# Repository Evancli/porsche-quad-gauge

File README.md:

# QUAD GAUGE FOR A PORSCHE 914
More info [here](https://evanli.com/quad-gauge-for-a-porsche-914/).

## Required Items
This gauge uses salvaged components from a Porsche 944 fuel gauge; the bezel, glass, and face plate. You can used the vintage gauges from the 944 or the corresponding gauges from your 914. It also required two new VDO gauges for voltage and oil pressure.

## Disassembly Tips
It's quite laborious to open these VDO gauges, even with the right tools. A prying spudger and flat implement are needed. Lots of care and attention to not mess up the sheet metal. Be very careful when you pry open the 944 fuel gauge. It's very easy damage the surface finish of the bezel. 

## Processes
The build uses 3D printed parts as well a laser cut and etched parts. 

## License
Shield: [![CC BY-SA 4.0][cc-by-sa-shield]][cc-by-sa]

This work is licensed under a
[Creative Commons Attribution-ShareAlike 4.0 International License][cc-by-sa].

[![CC BY-SA 4.0][cc-by-sa-image]][cc-by-sa]

[cc-by-sa]: http://creativecommons.org/licenses/by-sa/4.0/
[cc-by-sa-image]: https://licensebuttons.net/l/by-sa/4.0/88x31.png
[cc-by-sa-shield]: https://img.shields.io/badge/License-CC%20BY--SA%204.0-lightgrey.svg

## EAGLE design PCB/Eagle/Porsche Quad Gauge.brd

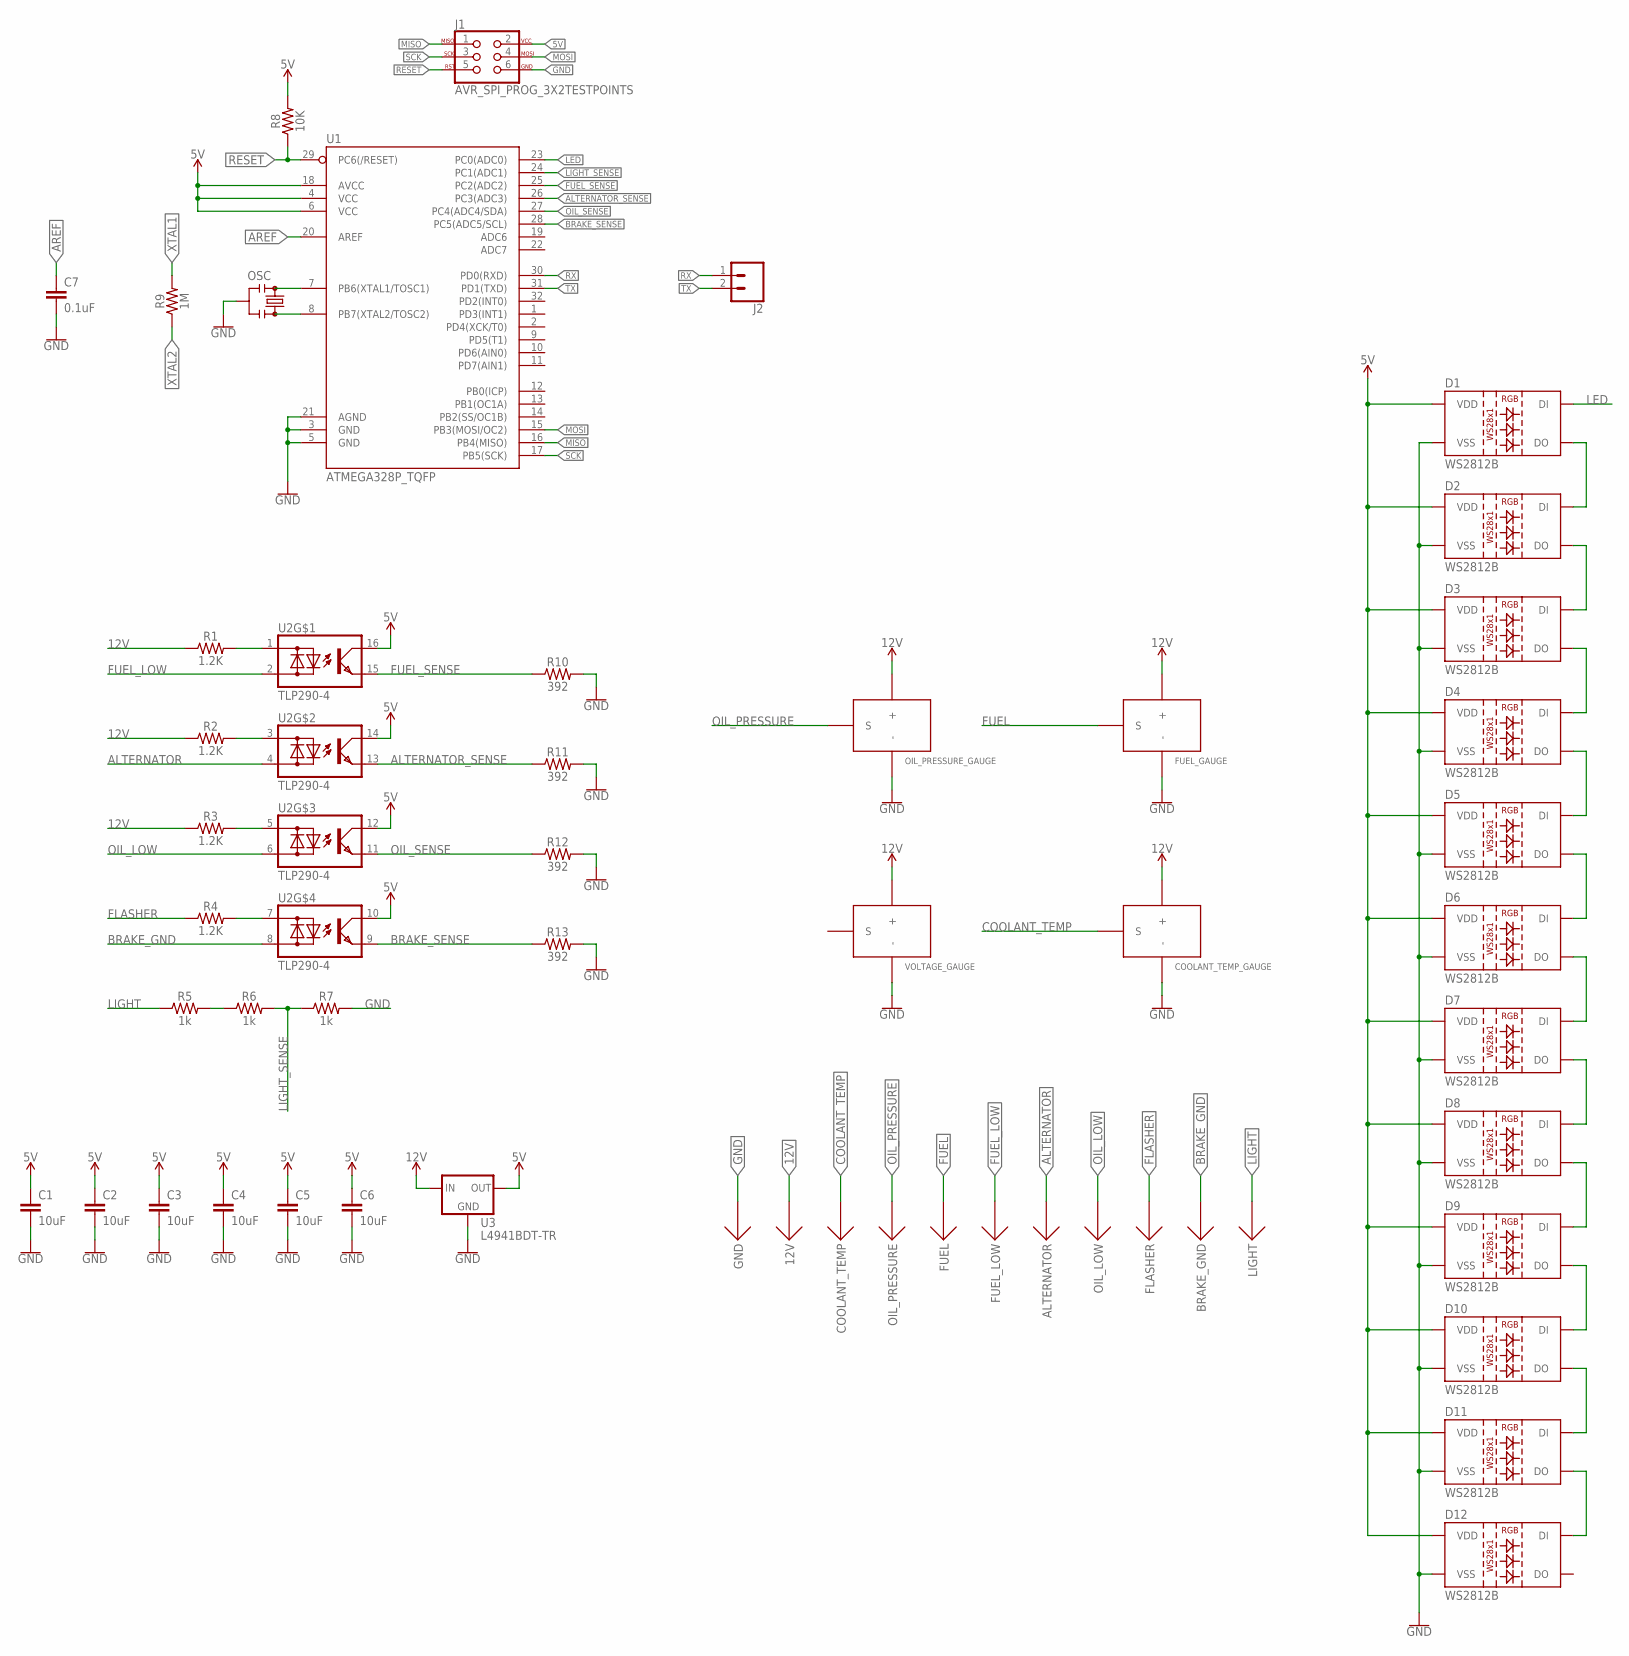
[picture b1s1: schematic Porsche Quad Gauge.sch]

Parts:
12V: CONNECTOR_QC_TAB_0.25; CONNECTOR_QC_TAB-0.25
ALTERNATOR: CONNECTOR_QC_TAB_0.25; CONNECTOR_QC_TAB-0.25
BRAKE_GND: CONNECTOR_QC_TAB_0.25; CONNECTOR_QC_TAB-0.25
C1, C2, C3, C4, C5, C6: 10uF; 0805
C7: 0.1uF; 0805
COOLANT_TEMP: CONNECTOR_QC_TAB_0.25; CONNECTOR_QC_TAB-0.25
COOLANT_TEMP_GAUGE: VDO_OLD; VDO_GAUGE_SOCKET
D1, D2, D3, D4, D5, D6, D7, D8, D9, D10, D11, D12: WS2812B
FLASHER: CONNECTOR_QC_TAB_0.25; CONNECTOR_QC_TAB-0.25
FUEL: CONNECTOR_QC_TAB_0.25; CONNECTOR_QC_TAB-0.25
FUEL_GAUGE: VDO_OLD; VDO_GAUGE_SOCKET
FUEL_LOW: CONNECTOR_QC_TAB_0.25; CONNECTOR_QC_TAB-0.25
GND: CONNECTOR_QC_TAB_0.25; CONNECTOR_QC_TAB-0.25
J1: AVR_SPI_PROG_3X2TESTPOINTS; 2X3_TEST_POINTS
J2: CONN_02; 1X02
LIGHT: CONNECTOR_QC_TAB_0.25; CONNECTOR_QC_TAB-0.25
OIL_LOW: CONNECTOR_QC_TAB_0.25; CONNECTOR_QC_TAB-0.25
OIL_PRESSURE: CONNECTOR_QC_TAB_0.25; CONNECTOR_QC_TAB-0.25
OIL_PRESSURE_GAUGE: VDO_NEW; VDO_NEW_GAUGE_SOCKET
OSC: PRQC16.00SR1010V00L; 3-SMD
R1, R2, R3, R4: 1.2K; 0805
R5, R6, R7: 1k; 0805
R8: 10K; 0805
R9: 1M; 0805
R10, R11, R12, R13: 392; 0805
U1: ATMEGA328P_TQFP; TQFP32-08
U2: TLP290-4; SO16
U3: L4941BDT-TR; D-PAK_TO252AA
VOLTAGE_GAUGE: VDO_NEW; VDO_NEW_GAUGE_SOCKET

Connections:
5V: C1.1, C2.1, C3.1, C4.1, C5.1, C6.1, D1.1 (VDD), D2.1 (VDD), D3.1 (VDD), D4.1 (VDD), D5.1 (VDD), D6.1 (VDD), D7.1 (VDD), D8.1 (VDD), D9.1 (VDD), D10.1 (VDD), D11.1 (VDD), D12.1 (VDD), J1.2, R8.2, U1.4 (VCC), U1.6 (VCC), U1.18 (AVCC), U2.10 (C), U2.12 (C), U2.14 (C), U2.16 (C), U3.3 (OUT)
12V: 12V.S1, 12V.S2, COOLANT_TEMP_GAUGE.12V (+), FUEL_GAUGE.12V (+), OIL_PRESSURE_GAUGE.12V (+), R1.1, R2.1, R3.1, U3.1 (IN), VOLTAGE_GAUGE.12V (+)
ALTERNATOR: ALTERNATOR.S1, ALTERNATOR.S2, U2.4 (AC2)
ALTERNATOR_SENSE: R11.1, U1.26 (PC3(ADC3)), U2.13 (E)
AREF: C7.1, U1.20 (AREF)
BRAKE_GND: BRAKE_GND.S1, BRAKE_GND.S2, U2.8 (AC2)
BRAKE_SENSE: R13.1, U1.28 (PC5(ADC5/SCL)), U2.9 (E)
COOLANT_TEMP: COOLANT_TEMP.S1, COOLANT_TEMP.S2, COOLANT_TEMP_GAUGE.SIGNAL (S)
FLASHER: FLASHER.S1, FLASHER.S2, R4.1
FUEL: FUEL.S1, FUEL.S2, FUEL_GAUGE.SIGNAL (S)
FUEL_LOW: FUEL_LOW.S1, FUEL_LOW.S2, U2.2 (AC2)
FUEL_SENSE: R10.1, U1.25 (PC2(ADC2)), U2.15 (E)
GND: C1.2, C2.2, C3.2, C4.2, C5.2, C6.2, C7.2, COOLANT_TEMP_GAUGE.GND (-), D1.3 (VSS), D2.3 (VSS), D3.3 (VSS), D4.3 (VSS), D5.3 (VSS), D6.3 (VSS), D7.3 (VSS), D8.3 (VSS), D9.3 (VSS), D10.3 (VSS), D11.3 (VSS), D12.3 (VSS), FUEL_GAUGE.GND (-), GND.S1, GND.S2, J1.6, OIL_PRESSURE_GAUGE.GND (-), OSC.GND (2), R7.2, R10.2, R11.2, R12.2, R13.2, U1.3 (GND), U1.5 (GND), U1.21 (AGND), U3.2 (GND), VOLTAGE_GAUGE.GND (-)
LED: D1.4 (DI), U1.23 (PC0(ADC0))
LIGHT: LIGHT.S1, LIGHT.S2, R5.1
LIGHT_SENSE: R6.2, R7.1, U1.24 (PC1(ADC1))
MISO: J1.1, U1.16 (PB4(MISO))
MOSI: J1.4, U1.15 (PB3(MOSI/OC2))
unnamed: R1.2, U2.1 (AC1)
unnamed: R5.2, R6.1
unnamed: R2.2, U2.3 (AC1)
unnamed: D1.2 (DO), D2.4 (DI)
unnamed: D2.2 (DO), D3.4 (DI)
unnamed: D3.2 (DO), D4.4 (DI)
unnamed: D4.2 (DO), D5.4 (DI)
unnamed: D5.2 (DO), D6.4 (DI)
unnamed: D6.2 (DO), D7.4 (DI)
unnamed: D7.2 (DO), D8.4 (DI)
unnamed: D8.2 (DO), D9.4 (DI)
unnamed: D9.2 (DO), D10.4 (DI)
unnamed: D10.2 (DO), D11.4 (DI)
unnamed: D11.2 (DO), D12.4 (DI)
unnamed: R3.2, U2.5 (AC1)
unnamed: R4.2, U2.7 (AC1)
OIL_LOW: OIL_LOW.S1, OIL_LOW.S2, U2.6 (AC2)
OIL_PRESSURE: OIL_PRESSURE.S1, OIL_PRESSURE.S2, OIL_PRESSURE_GAUGE.SIGNAL (S)
OIL_SENSE: R12.1, U1.27 (PC4(ADC4/SDA)), U2.11 (E)
RESET: J1.5, R8.1, U1.29 (PC6(/RESET))
RX: J2.1, U1.30 (PD0(RXD))
SCK: J1.3, U1.17 (PB5(SCK))
TX: J2.2, U1.31 (PD1(TXD))
XTAL1: OSC.XTAL1 (1), R9.2, U1.7 (PB6(XTAL1/TOSC1))
XTAL2: OSC.XTAL2 (3), R9.1, U1.8 (PB7(XTAL2/TOSC2))

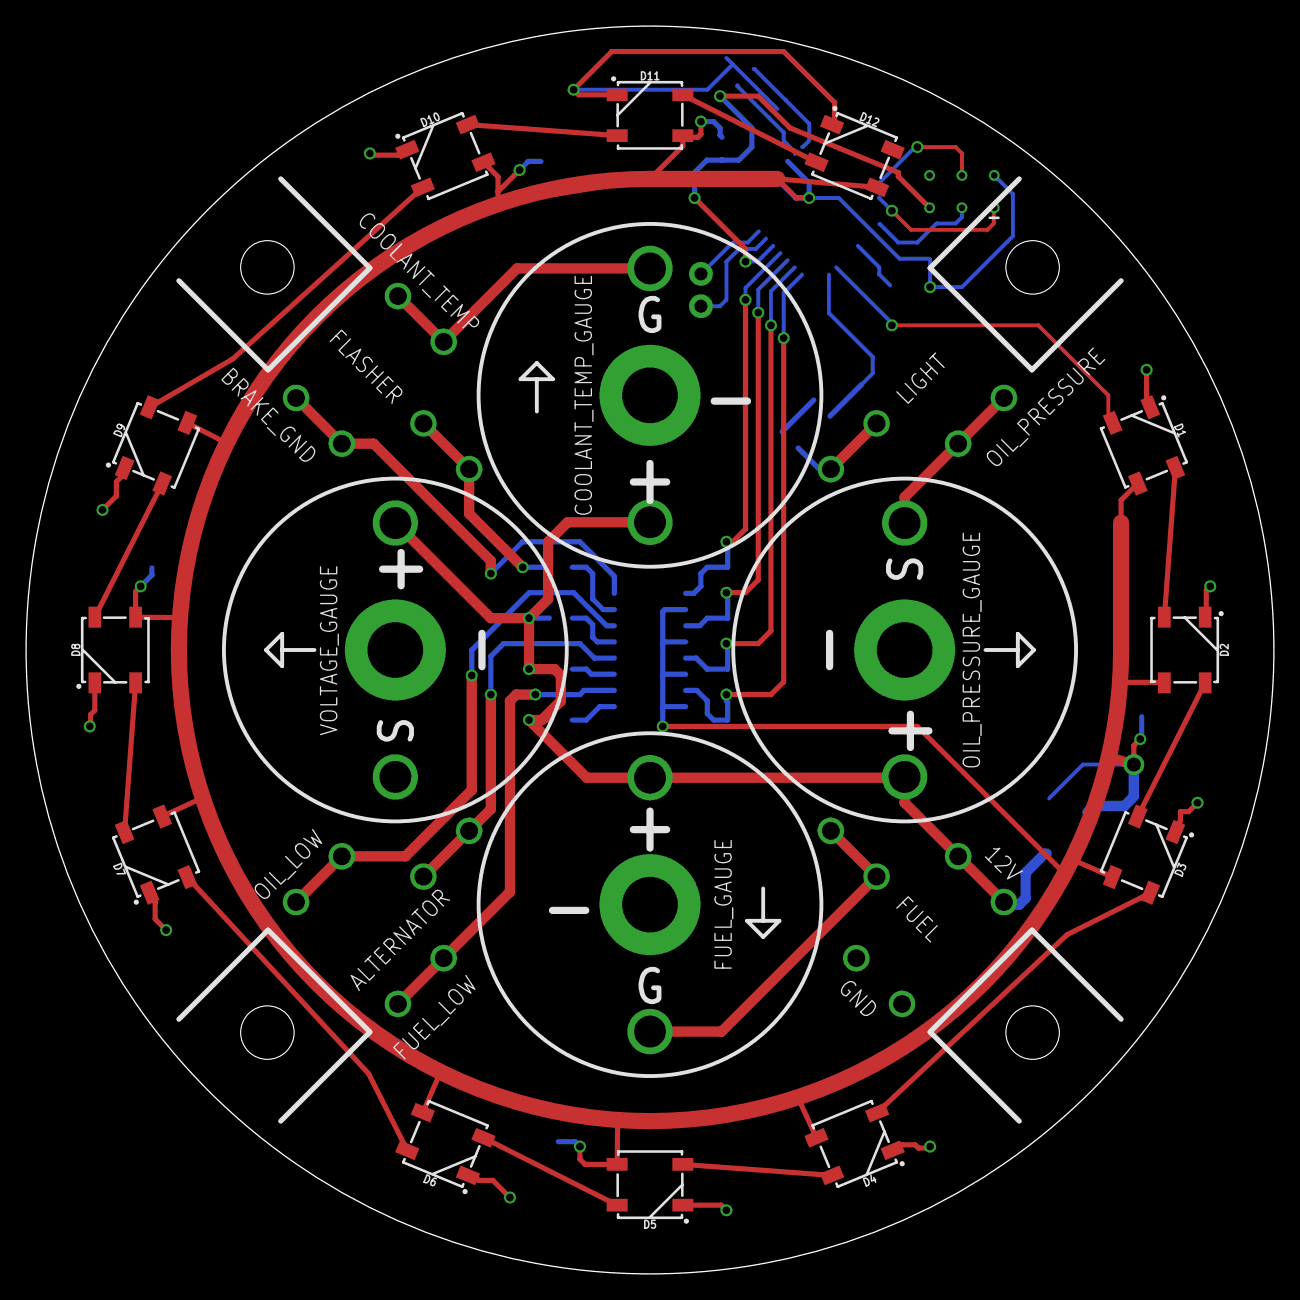
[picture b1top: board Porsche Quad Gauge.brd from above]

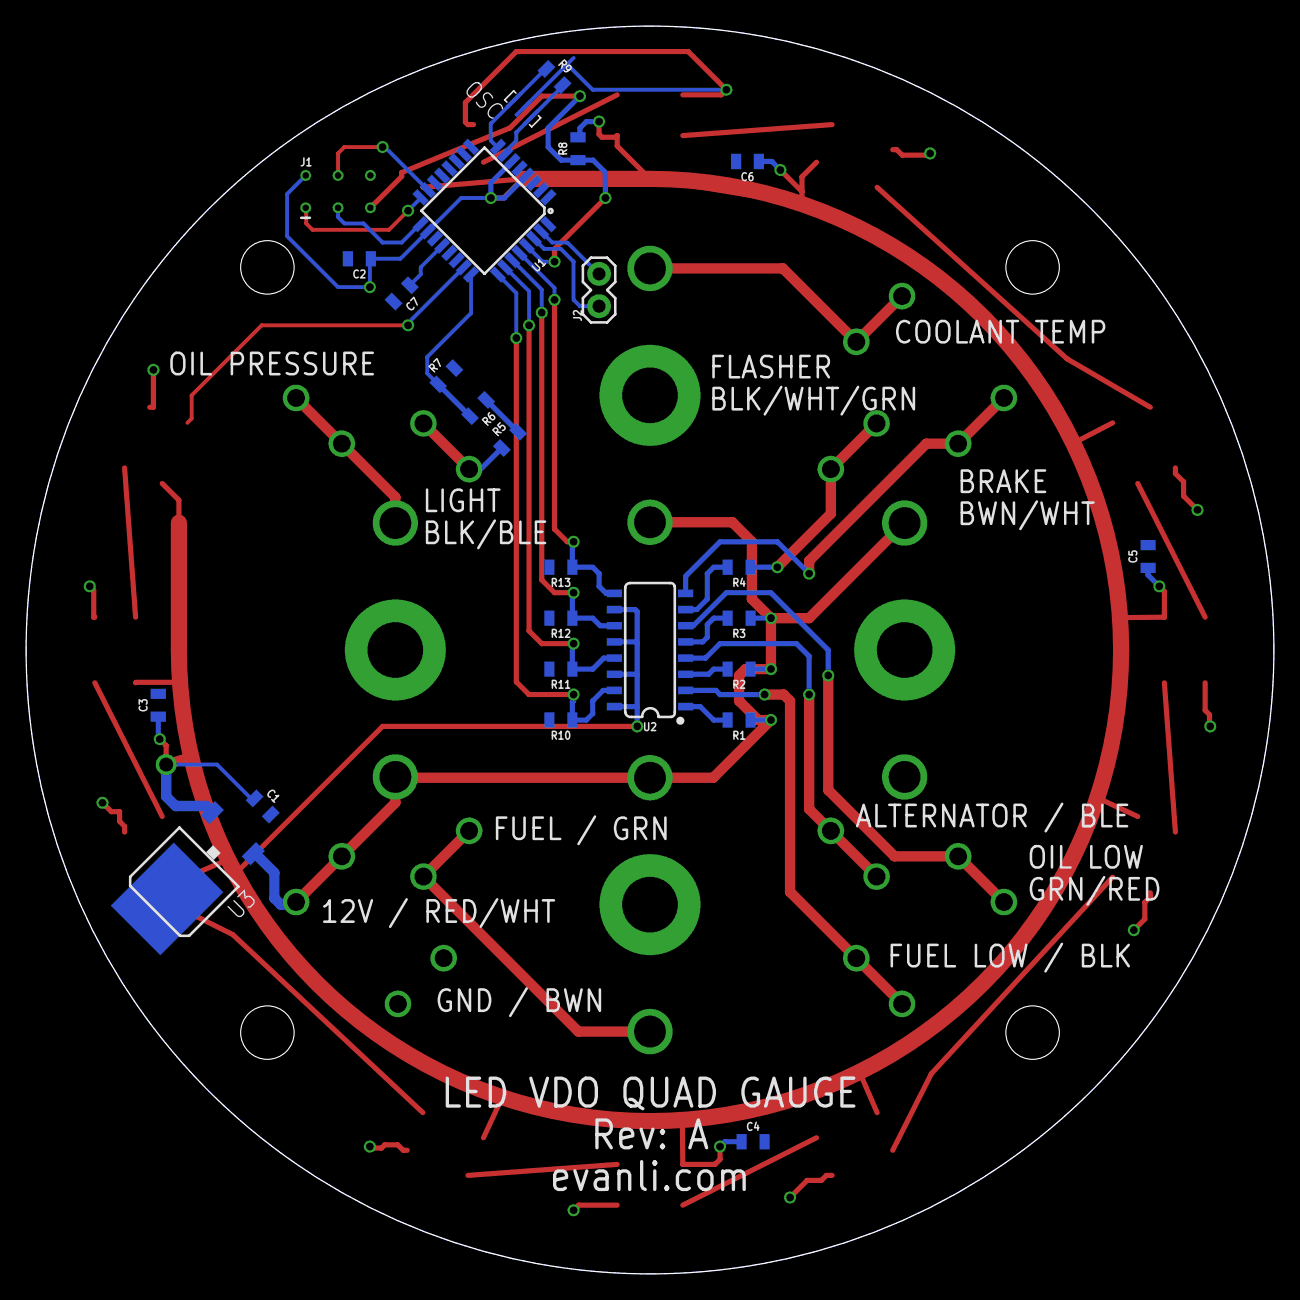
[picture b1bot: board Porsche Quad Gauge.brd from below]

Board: 2 copper layers, 98.0 x 98.0 mm, 53 parts (26 on the bottom side), 43 nets.

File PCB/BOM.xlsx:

Item # | Qty | Ref Des | Manufacturer | Manufacturer Part Num | Value | Package | Type | Digikey Part Num | Desciption
1 | 11 | QC Connector | TE Connectivity AMP Connectors | 63824-1 |  |  | Through Hole | A29938CT-ND | CONN QC TAB 0.250 SOLDER
2 | 6 | C1, C2, C3, C4, C5, C6 |  |  | 10uF | 0805 | SMT
3 | 1 | C7 |  |  | 0.1uF | 0805 | SMT
4 | 12 | D1, D2, D3, D4, D5, D6, D7, D8, D9, D10, D11, D12 |  | SK6812 RGBW LED |  |  | SMT
5 | 4 or 8 | Gauge Interface Pin (Depends on VDO Gauge Used) | Keystone Electronics | 1223 | 0.267"" (6.78mm) |  | Through Hole | 36-1223-ND | CONN PC PIN CIRC 0.093DIA NICKEL
6 | 4 or 8 | Gauge Interface Pin (Depends on VDO Gauge Used) | Keystone Electronics | 1224 | 0.331"" (8.41mm) |  | Through Hole | 36-1224-ND | CONN PC PIN CIRC 0.093DIA NICKEL
7 | 1 | OSC1 | Kyocera International Inc. | PRQC16.00CR5010X000 | 16MHz | 3-SMD, Non-Standard | SMT | 1253-1675-1-ND | CERAMIC RES 16.0000MHZ 10PF SMD
8 | 4 | R1, R2, R3, R4 |  |  | 1.2K Ohms 5% 1/8W | 0805 | SMT
9 | 3 | R5, R6, R7 |  |  | 1K Ohms 5% 1/8W | 0805 | SMT
10 | 1 | R8 |  |  | 10K Ohms 5% 1/8W | 0805 | SMT
11 | 1 | R9 |  |  | 1M Ohms 5% 1/8W | 0805 | SMT
12 | 4 | R10, R11, R12, R13 |  |  | 392 Ohms 5% 1/8W | 0805 | SMT
13 | 1 | U1 | Microchip Technology | ATMEGA328PB-ANR |  | 32-TQFP | SMT | ATMEGA328PB-ANRCT-ND | IC MCU 8BIT 32KB FLASH 32TQFP
14 | 1 | U2 | Toshiba Semiconductor and Storage | TLP290-4(GB,E) |  | 16-SOIC | SMT | TLP290-4(GBE)-ND | OPTOISOLTR 2.5KV 4CH TRANS 16-SO
15 | 1 | U3 | STMicroelectronics | L4941BDT-TR |  | DPAK | SMT | 497-1168-1-ND | IC REG LINEAR 5V 1A DPAK

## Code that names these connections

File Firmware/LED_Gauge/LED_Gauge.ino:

#include <Arduino.h>

#include <Adafruit_NeoPixel.h>

#ifdef __AVR__
  #include <avr/power.h>
#endif

#define LED_PIN 14
#define LIGHT_SENSE A1
#define FUEL_SENSE 16
#define ALTERNATOR_SENSE 17
#define OIL_SENSE 18
#define BRAKE_SENSE 19

#define MAX_BRIGHTNESS 128

#define LED_COUNT 12

// Ref: https://learn.adafruit.com/adafruit-neopixel-uberguide/arduino-library
Adafruit_NeoPixel leds = Adafruit_NeoPixel(LED_COUNT, LED_PIN, NEO_RGBW + NEO_KHZ800);

int lightSenseValue = 0;
int fuelSenseValue = 0;
int alternatorSenseValue = 0;
int oilSenseValue = 0;
int brakeSenseValue = 0;

int brightnessValue = 0;

/// RGBW seems to be GRBW
uint32_t fuelColor = leds.Color(128, 255, 0, 0); // leds.Color(255, 128, 0, 0);
uint32_t alternatorColor = leds.Color(0, 255, 0, 0);
uint32_t oilColor = leds.Color(255, 0, 0, 0);
uint32_t brakeColor = leds.Color(0, 255, 0, 0);

void setup() {

  pinMode(FUEL_SENSE, INPUT);
  pinMode(ALTERNATOR_SENSE, INPUT);
  pinMode(OIL_SENSE, INPUT);
  pinMode(BRAKE_SENSE, INPUT);

  leds.setBrightness(MAX_BRIGHTNESS);

  leds.begin();
  leds.show();
}

void loop() {

  lightSenseValue = analogRead(LIGHT_SENSE);
  fuelSenseValue = digitalRead(FUEL_SENSE);
  alternatorSenseValue = digitalRead(ALTERNATOR_SENSE);
  oilSenseValue = digitalRead(OIL_SENSE);
  brakeSenseValue = digitalRead(BRAKE_SENSE);



  brightnessValue = map(lightSenseValue, 0, 1023, 0, 128);



  for (int i = 0; i < LED_COUNT; i++) {
    leds.setPixelColor(i, leds.Color(0, 0, 0, brightnessValue));

    if (i >= 0 && i < 3 && oilSenseValue) {
      leds.setPixelColor(i, oilColor );
    }

    if (i >= 3  && i < 6 && fuelSenseValue) {
      leds.setPixelColor(i, fuelColor );
    }

    if (i >= 6 && i < 9 && alternatorSenseValue) {
      leds.setPixelColor(i, alternatorColor);
    }

    if (i >= 9 && i < 12 && brakeSenseValue) {
      leds.setPixelColor(i, brakeColor);
    }
  }


//  for (int i = 0; i < 24; i++) {
//    if (i < brightness) {
//      leds.setPixelColor(i, leds.Color(255, 0, 0));
//    } else {
//      leds.setPixelColor(i, leds.Color(0, 0, 0));
//    }
//  }

  leds.show();
  delay(50);
}

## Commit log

2020-12-14 Technical information packet.
2020-12-15 Update README.md
    Added more information.

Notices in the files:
parts and their libraries:
SparkFun-Resistors: Licensing: Creative Commons ShareAlike 4.0 International - https://creativecommons.org/licenses/by-sa/4.0
